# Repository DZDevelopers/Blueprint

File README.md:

# Blueprint
Micro Keyboard / Hackpad 

An 8-key (2×4) mechanical macropad powered by a Seeed Studio XIAO RP2040, designed as a simple and compact hackpad for macros, shortcuts, and experimentation.

This project is fully open-source and includes schematics, PCB design, and a simple enclosure.

Overall Hackpad

Schematic

PCB

Hardware Overview

Microcontroller: Seeed Studio XIAO RP2040

Switches: Cherry MX compatible mechanical switches

LEDs: SK6812 Mini RGB LEDs (per key)

Layout: 2 rows × 4 columns

Use case: Macros, shortcuts, gaming, and productivity

Bill of Materials (BOM)

2 × SK6812 Mini RGB LEDs

8 × Cherry MX mechanical keyboard switches

1 × XIAO-RP2040-DIP microcontroller

1 × Custom-designed PCB

1 × Case (3D-printed)

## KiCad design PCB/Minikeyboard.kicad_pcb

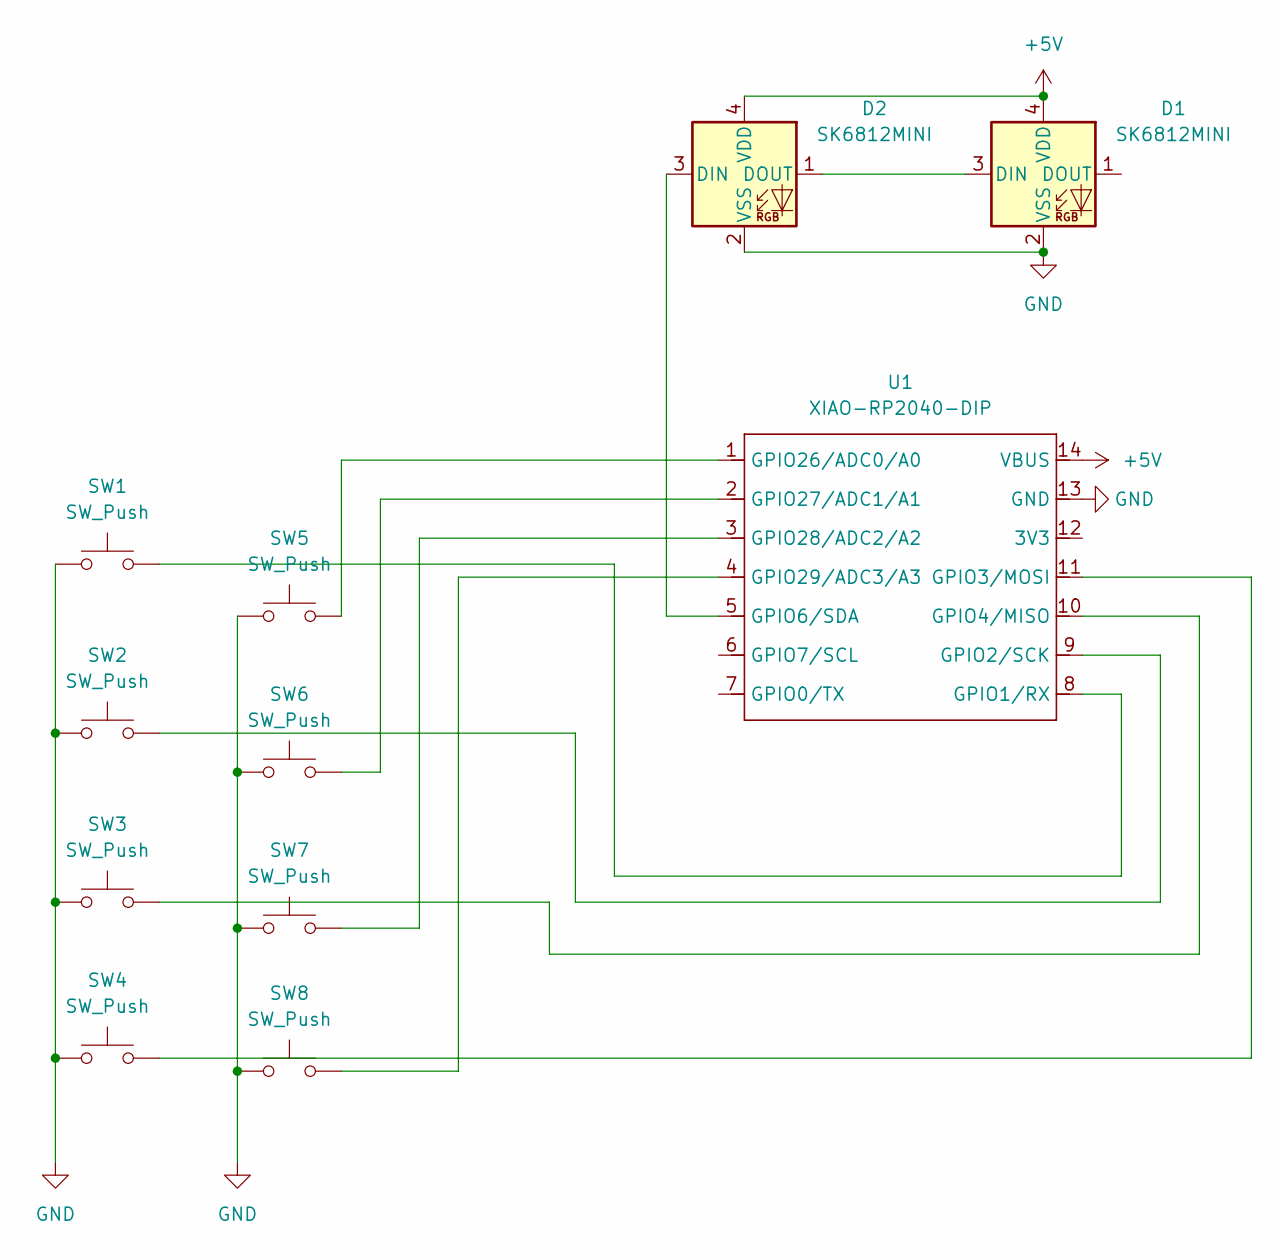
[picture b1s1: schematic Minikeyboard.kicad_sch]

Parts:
D1, D2: SK6812MINI; LED_SK6812MINI_PLCC4_3.5x3.5mm_P1.75mm
SW1, SW2, SW3, SW4, SW5, SW6, SW7, SW8: SW_Push; SW_Cherry_MX_1.00u_PCB
U1: XIAO-RP2040-DIP

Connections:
+5V: D1.4 (VDD), D2.4 (VDD), U1.14 (VBUS)
GND: D1.2 (VSS), D2.2 (VSS), SW1.1, SW2.1, SW3.1, SW4.1, SW5.1, SW6.1, SW7.1, SW8.1, U1.13 (GND)
unnamed: D1.3 (DIN), D2.1 (DOUT)
unnamed: D2.3 (DIN), U1.5 (GPIO6/SDA)
unnamed: SW1.2, U1.8 (GPIO1/RX)
unnamed: SW2.2, U1.9 (GPIO2/SCK)
unnamed: SW4.2, U1.11 (GPIO3/MOSI)
unnamed: SW3.2, U1.10 (GPIO4/MISO)
unnamed: SW5.2, U1.1 (GPIO26/ADC0/A0)
unnamed: SW6.2, U1.2 (GPIO27/ADC1/A1)
unnamed: SW7.2, U1.3 (GPIO28/ADC2/A2)
unnamed: SW8.2, U1.4 (GPIO29/ADC3/A3)

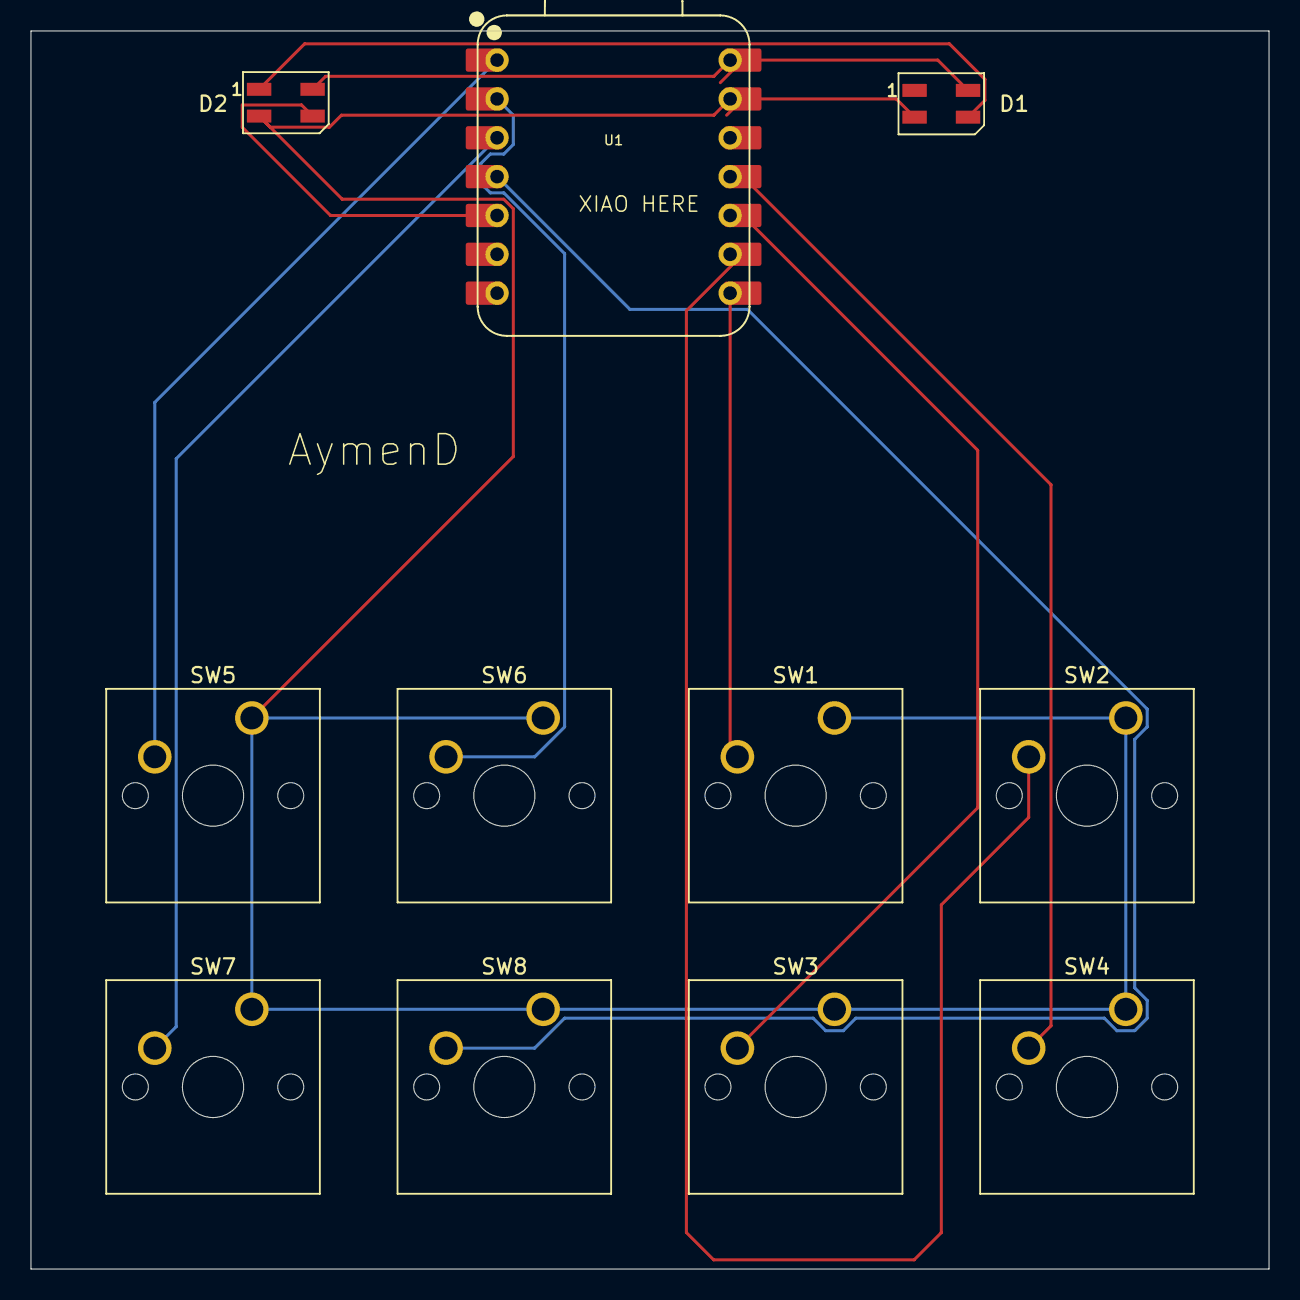
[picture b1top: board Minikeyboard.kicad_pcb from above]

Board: 2 copper layers, 81.0 x 81.0 mm, 11 parts (0 on the bottom side), 12 nets.

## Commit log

2025-12-19 Fixed Everything
2025-12-19 Revise README for hardware overview and features
